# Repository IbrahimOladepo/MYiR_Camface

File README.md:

# MYiR_Camface
This is a PCB to interface regular 22-pin MIPI cameras to the 24-pin MYiR dev boards. 

## PCB Render

## Impedance Calculation

Differential impedance for the MIPI CSI pairs, calculated with the JLCPCB impedance calculator.

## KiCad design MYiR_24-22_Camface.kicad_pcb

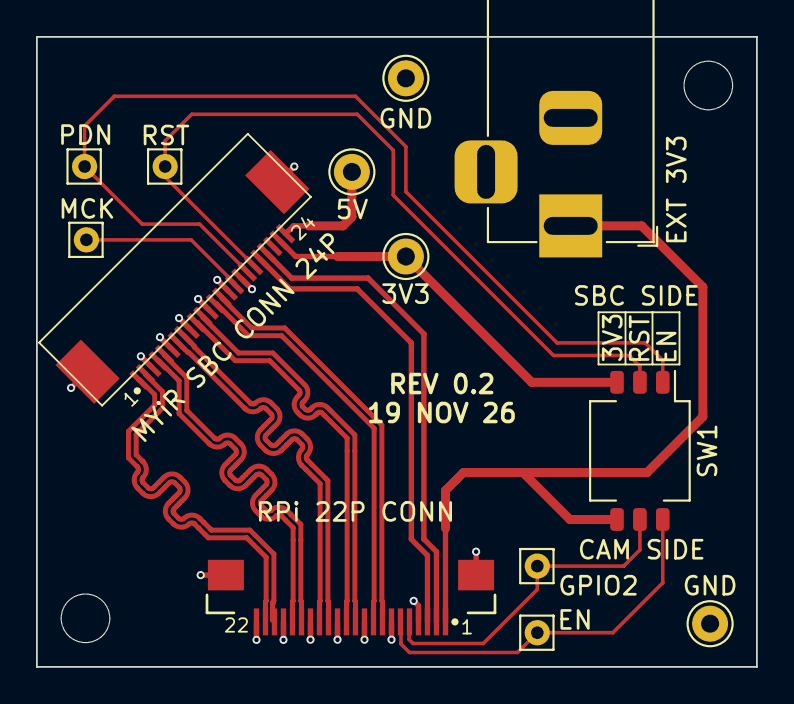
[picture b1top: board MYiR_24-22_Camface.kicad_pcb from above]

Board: 2 copper layers, 40.0 x 35.0 mm, 15 parts (0 on the bottom side), 21 nets.

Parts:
3V3, 5V: PTH; Pin_D1.0mm_L10.0mm
EN: PTH; Pin_D0.7mm_L6.5mm_W1.8mm_FlatFork
GND: PTH; Pin_D1.0mm_L10.0mm
GND#2: PTH; Pin_D1.0mm_L10.0mm
GPIO2: PTH; Pin_D0.7mm_L6.5mm_W1.8mm_FlatFork
H1, H2: MH; MountingHole_2.7mm_M2.5_DIN965
J1: Conn_01x22_FPC_0.5mm; FPC_1x22_P0.5mm_Horizontal_BottomContact
J2: Conn_01x24_FPC; FPC_1x24_P0.5mm_Horizontal_BottomContact
J3: JACK_3V3; BarrelJack_Horizontal
MCK: PTH; Pin_D0.7mm_L6.5mm_W1.8mm_FlatFork
PDN: PTH; Pin_D0.7mm_L6.5mm_W1.8mm_FlatFork
RST: PTH; Pin_D0.7mm_L6.5mm_W1.8mm_FlatFork
SW1: SW_DIP_x03; SW_DIP_SPSTx03_Slide_KingTek_DSHP03TS_W7.62mm_P1.27mm

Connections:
+3.3V: 3V3.1 (1_1), J2.23, SW1.3
+3.3V-PI: J1.1, J3.1, SW1.4
+5V: 5V.1 (1_1), J2.24
/CKN: J1.15, J2.7
/CKP: J1.14, J2.8
/D0N: J1.21, J2.1
/D0P: J1.20, J2.2
/D1N: J1.18, J2.4
/D1P: J1.17, J2.5
/D2N: J1.12, J2.10
/D2P: J1.11, J2.11
/D3N: J1.9, J2.13
/D3P: J1.8, J2.14
/EN: EN.1 (1_1), J1.6, SW1.6
/GPIO2: GPIO2.1 (1_1), J1.5, SW1.5
/MCLK: J2.16, MCK.1 (1_1)
/PWDN: J2.18, PDN.1 (1_1), SW1.1
/RST: J2.19, RST.1 (1_1), SW1.2
/SCL: J1.3, J2.20
/SDA: J1.2, J2.21
GND: GND.1 (1_1), GND#2.1 (1_1), J1.4, J1.7, J1.10, J1.13, J1.16, J1.19, J1.22, J1.MNT1, J1.MNT2, J2.3, J2.6, J2.9, J2.12, J2.15, J2.17, J2.MNT1, J2.MNT2, J3.2, J3.3

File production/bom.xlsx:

Designator | Footprint | Quantity | Value | LCSC Part #
J1 | FPC_1x22_P0.5mm_Horizontal_BottomContact | 1 | Conn_01x22_FPC_0.5mm | C22360344
J2 | FPC_1x24_P0.5mm_Horizontal_BottomContact | 1 | Conn_01x24_FPC | C3446015
